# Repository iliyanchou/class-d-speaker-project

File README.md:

# Class-D Active Speaker Project

This repository presents my diploma engineering project: an active speaker system built around a Class-D amplifier.

## Overview

The project focuses on the design and practical implementation of an active speaker with efficient amplification, wireless audio input, analog input, tone control, and support for external subwoofer connection.

The system combines electronics, acoustics, amplifier theory, digital audio concepts, Bluetooth communication, power supply design, and physical construction.

## Main goals

* Build an active speaker with good sound quality and low distortion
* Use a Class-D amplifier for high efficiency and compact design
* Support Bluetooth audio and AUX input
* Add tone correction and signal control
* Design a portable and practical physical construction
* Document the theory, implementation, and testing process

## Key technologies and topics

* Class-D audio amplification
* PWM-based signal amplification
* Speaker and acoustic enclosure basics
* DSP and digital/analog audio conversion
* Bluetooth audio transmission
* Power supply and battery pack design
* Practical hardware assembly

## Documentation

The full diploma documentation is available in the `docs/` folder.

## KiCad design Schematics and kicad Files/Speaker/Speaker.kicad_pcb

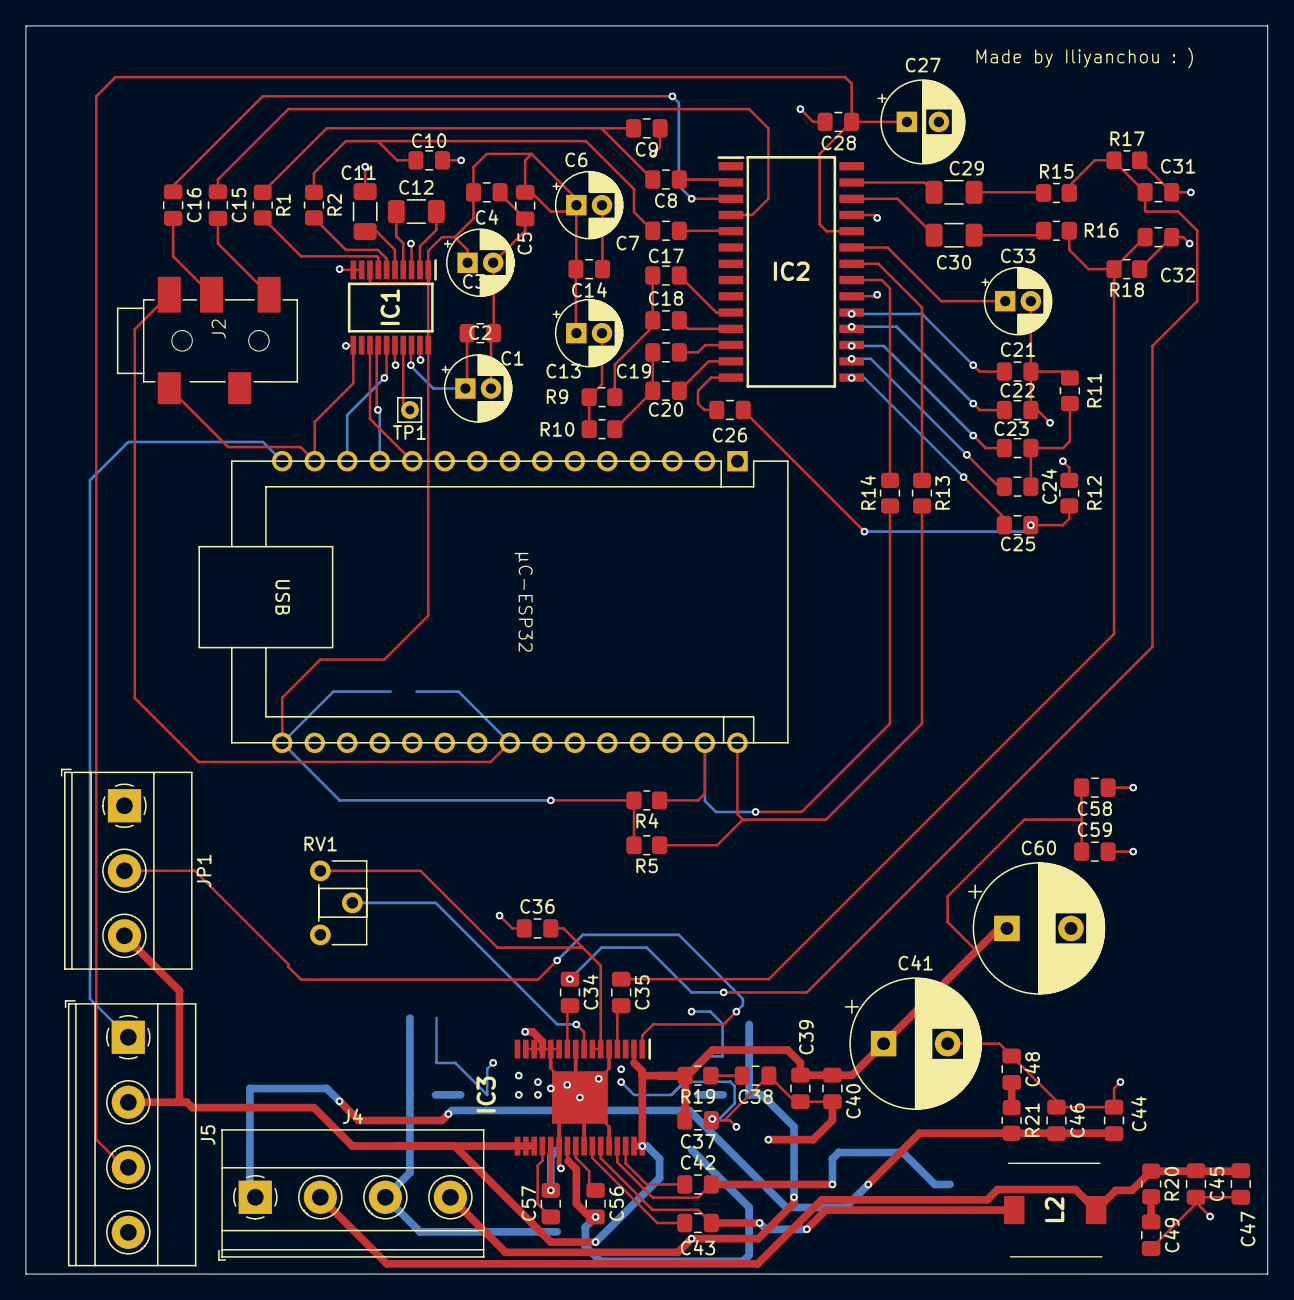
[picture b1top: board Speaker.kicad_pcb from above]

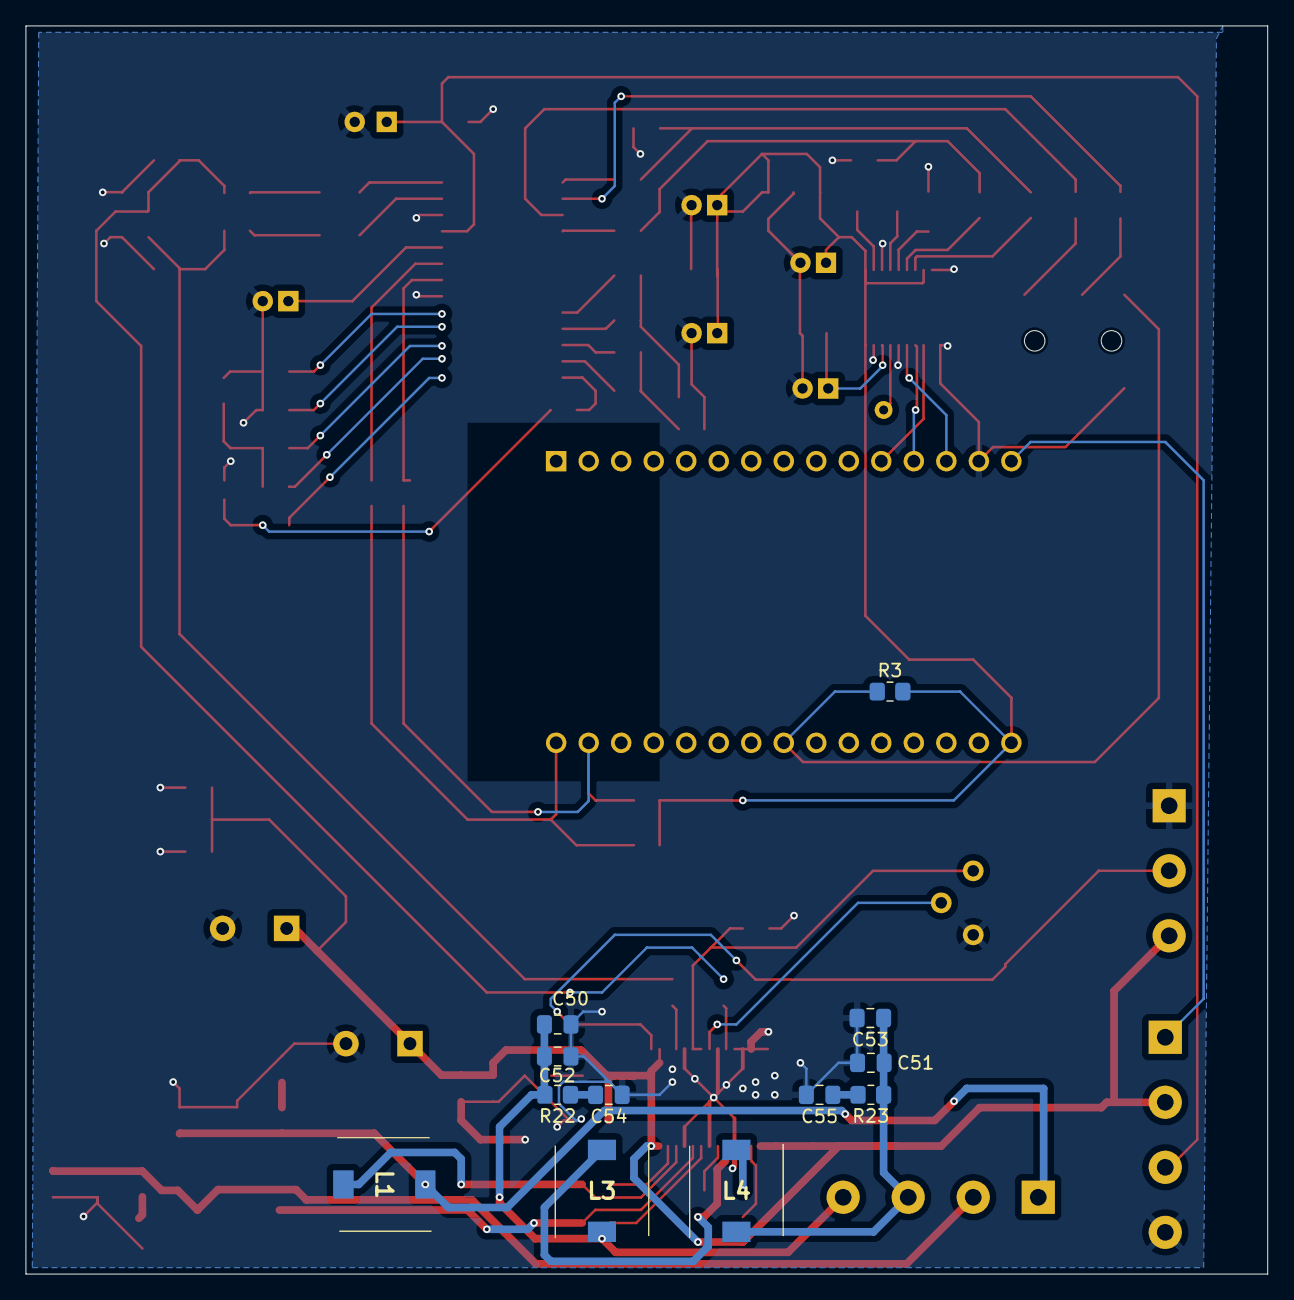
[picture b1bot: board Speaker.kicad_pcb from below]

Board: 2 copper layers, 97.0 x 97.5 mm, 94 parts (12 on the bottom side), 71 nets.

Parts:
C1, C3, C6, C13, C33: 10µF; CP_Radial_D5.0mm_P2.00mm
C2, C4, C5, C14, C19, C20, C25, C26, C28, C38, C40, C59: 100nF; C_0805_2012Metric_Pad1.18x1.45mm_HandSolder
C7, C8, C15, C16: 470nF; C_0805_2012Metric_Pad1.18x1.45mm_HandSolder
C9, C10: 2.2nF; C_0805_2012Metric_Pad1.18x1.45mm_HandSolder
C11, C12, C29, C30: 2.2µF; C_1206_3216Metric_Pad1.33x1.80mm_HandSolder
C17, C23: 18nF; C_0805_2012Metric_Pad1.18x1.45mm_HandSolder
C18, C24: 22nF; C_0805_2012Metric_Pad1.18x1.45mm_HandSolder
C21, C22: 5.6nF; C_0805_2012Metric_Pad1.18x1.45mm_HandSolder
C27: 47µF; CP_Radial_D6.3mm_P2.50mm
C31, C32, C39, C46, C47, C52, C53, C58: 1nF; C_0805_2012Metric_Pad1.18x1.45mm_HandSolder
C34, C35, C36: 1µF; C_0805_2012Metric_Pad1.18x1.45mm_HandSolder
C37, C48, C49, C54, C55: 10nF; C_0805_2012Metric_Pad1.18x1.45mm_HandSolder
C41, C60: 220µF; CP_Radial_D10.0mm_P5.00mm
C42, C43, C56, C57: 220nF; C_0805_2012Metric_Pad1.18x1.45mm_HandSolder
C44, C45, C50, C51: 680nF; C_0805_2012Metric_Pad1.18x1.45mm_HandSolder
IC1: PCM5102APWR; SOP65P640X120-20N
IC2: TDA7439DS13TR; SOIC127P1032X265-28N
IC3: TPA3129D2DAP; SOP65P810X120-33N
J2: Jack
J4, J5: Screw_Terminal_01x04; TerminalBlock_Phoenix_MKDS-1,5-4-5.08_1x04_P5.08mm_Horizont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
JP1: Jumper_3_Bridged12; TerminalBlock_Phoenix_MKDS-1,5-3-5.08_1x03_P5.08mm_Horizont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
L1, L2, L3, L4: 10µH; CDRH74NP220MCB
R1, R2, R13, R14: 470Ω; R_0805_2012Metric_Pad1.20x1.40mm_HandSolder
R3: 4.7kΩ; R_0805_2012Metric_Pad1.20x1.40mm_HandSolder
R4, R5, R17, R18: 10kΩ; R_0805_2012Metric_Pad1.20x1.40mm_HandSolder
R9, R11: 2.7kΩ; R_0805_2012Metric_Pad1.20x1.40mm_HandSolder
R10, R12: 5.6kΩ; R_0805_2012Metric_Pad1.20x1.40mm_HandSolder
R15, R16: 100Ω; R_0805_2012Metric_Pad1.20x1.40mm_HandSolder
R19: 33Ω; R_0805_2012Metric_Pad1.20x1.40mm_HandSolder
R20, R21, R22, R23: 3.3Ω; R_0805_2012Metric_Pad1.20x1.40mm_HandSolder
RV1: 120kΩ; Potentiometer_ACP_CA6-H2,5_Horizontal
TP1: MUTE; Pin_D0.7mm_L6.5mm_W1.8mm_FlatFork
µC-ESP32: ESP32

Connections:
3V3: C3.1, C4.2, C5.2, C6.1, C13.1, C14.2, IC1.1 (CPVDD), IC1.8 (AVDD), IC1.20 (DVDD), R3.2, R4.2, R5.2, µC-ESP32.1 (3v3)
5VCC: J5.1, µC-ESP32.30 (VIN)
9V VCC: C27.1, C28.1, IC2.24 (VS), J5.3
15VCC: C37.2, C39.2, C40.1, C41.1, C58.2, C59.1, C60.1, IC3.2 (SDZ), IC3.17 (AVCC), IC3.18 (PVCC_1), IC3.19 (PVCC_2), IC3.31 (PVCC_3), IC3.32 (PVCC_4), J5.2, JP1.3 (B), R19.2
GND: C1.2, C2.1, C3.2, C4.1, C5.1, C6.2, C9.1, C10.1, C11.1, C13.2, C14.1, C21.2, C22.2, C27.2, C28.2, C31.1, C32.2, C33.2, C36.1, C37.1, C38.1, C39.1, C40.2, C41.2, C44.1, C45.2, C46.1, C47.2, C48.1, C49.2, C50.1, C51.2, C52.1, C53.2, C54.1, C55.2, C58.1, C59.2, C60.2, IC1.3 (CPGND), IC1.9 (AGND), IC1.10 (DEMP), IC1.11 (FLT), IC1.16 (FMT), IC1.19 (DGND), IC2.20 (DIG-GND), IC2.25 (AGND), IC3.5 (RINN), IC3.9 (GND_1), IC3.11 (LINN), IC3.12 (MUTE), IC3.13 (AM2), IC3.14 (AM1), IC3.15 (AM0), IC3.22 (GND_2), IC3.25 (GND_3), IC3.28 (GND_4), IC3.33 (EP), J2.1 (GND), J5.4, JP1.1 (A), R9.2, R10.1, R11.2, R12.2, R17.2, R18.1, RV1.3, µC-ESP32.29 (GND)
unnamed: C8.2, C9.2, R1.1
unnamed: C7.2, C10.2, R2.1
unnamed: C17.1, C18.1, R9.1
unnamed: C19.1, C20.1, R10.2
unnamed: C23.2, C24.2, R11.1
unnamed: C25.2, C26.1, R12.1
unnamed: C29.2, R15.1
unnamed: C30.2, R16.1
unnamed: C31.2, C34.1, R15.2, R17.1
unnamed: C32.1, C35.1, R16.2, R18.2
unnamed: C38.2, R19.1
unnamed: C48.2, R21.1
unnamed: C49.1, R20.2
unnamed: C54.2, R22.1
unnamed: C55.1, R23.2
unnamed: IC1.13 (BCK), µC-ESP32.26 (D14)
unnamed: C12.1, IC1.4 (CAPM)
unnamed: C12.2, IC1.2 (CAPP)
unnamed: IC1.14 (DIN), µC-ESP32.27 (D12)
unnamed: C1.1, C2.2, IC1.18 (LDOO)
unnamed: IC1.15 (LRCK), µC-ESP32.28 (D13)
unnamed: IC1.6 (OUTL), R2.2
unnamed: IC1.7 (OUTR), R1.2
unnamed: C11.2, IC1.5 (VNEG)
unnamed: IC1.17 (XSMT), TP1.1
unnamed: C26.2, IC2.14 (BIN(L))
unnamed: C19.2, IC2.12 (BIN(R))
unnamed: C25.1, IC2.15 (BOUT(L))
unnamed: C20.2, IC2.13 (BOUT(R))
unnamed: C33.1, IC2.23 (CREF)
unnamed: C29.1, IC2.27 (LOUT)
unnamed: C15.1, IC2.4 (L_IN1)
unnamed: C7.1, IC2.5 (L_IN2)
unnamed: C23.1, IC2.17 (MIN(L))
unnamed: C17.2, IC2.10 (MIN(R))
unnamed: C24.1, IC2.16 (MOUT(L))
unnamed: C18.2, IC2.11 (MOUT(R))
unnamed: C30.1, IC2.26 (ROUT)
unnamed: C16.1, IC2.3 (R_IN1)
unnamed: C8.1, IC2.2 (R_IN2)
unnamed: IC2.21 (SCL), R14.2
unnamed: IC2.22 (SDA), R13.1
unnamed: C22.1, IC2.18 (TREBLE(L))
unnamed: C21.1, IC2.19 (TREBLE(R))
unnamed: C57.1, IC3.20 (BSNL)
unnamed: C43.1, IC3.26 (BSNR)
unnamed: C56.1, IC3.24 (BSPL)
unnamed: C42.1, IC3.30 (BSPR)
unnamed: IC3.8 (GAIN/SLV), RV1.2
unnamed: C36.2, IC3.6 (PLIMIT), IC3.7 (GVDD), RV1.1
unnamed: C34.2, IC3.10 (LINP)
unnamed: IC3.1 (MODSEL), JP1.2 (C)
unnamed: C57.2, IC3.21 (OUTNL), L4.2
unnamed: C43.2, IC3.27 (OUTNR), L2.2
unnamed: C56.2, IC3.23 (OUTPL), L3.1
unnamed: C42.2, IC3.29 (OUTPR), L1.1
unnamed: C35.2, IC3.4 (RINP)
unnamed: J2.5 (DETECT), R3.1, µC-ESP32.8 (D5)
unnamed: C15.2, J2.4 (L)
unnamed: C16.2, J2.3 (R)
unnamed: C44.2, C46.2, J4.1, L1.2, R21.2
unnamed: C45.1, C47.1, J4.2, L2.1, R20.1
unnamed: C51.1, C53.1, J4.3, L4.1, R23.1
unnamed: C50.2, C52.2, J4.4, L3.2, R22.2
unnamed: R4.1, R14.1, µC-ESP32.14 (D22)
unnamed: R5.1, R13.2, µC-ESP32.15 (D23)

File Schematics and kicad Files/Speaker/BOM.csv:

"Reference","Value","Datasheet","Footprint","Qty","DNP"
"4S1","14.8V / 3700mAh","~","","1",""
"AMSRL1-7805JZ1,J2,µC-ESP32","~","","-- mixed values --","3",""
"C1,C3,C6,C13,C33,C62,C63,C64","10µF","~","-- mixed values --","8",""
"C2,C4,C5,C14,C19,C20,C25,C26,C28,C38,C40,C59,C66,C67","100nF","~","Capacitor_SMD:C_0805_2012Metric_Pad1.18x1.45mm_HandSolder","14",""
"C7,C8,C15,C16","470nF","~","Capacitor_SMD:C_0805_2012Metric_Pad1.18x1.45mm_HandSolder","4",""
"C9,C10","2.2nF","~","Capacitor_SMD:C_0805_2012Metric_Pad1.18x1.45mm_HandSolder","2",""
"C11,C12,C29,C30","2.2µF","~","Capacitor_SMD:C_1206_3216Metric_Pad1.33x1.80mm_HandSolder","4",""
"C17,C23","18nF","~","Capacitor_SMD:C_0805_2012Metric_Pad1.18x1.45mm_HandSolder","2",""
"C18,C24","22nF","~","Capacitor_SMD:C_0805_2012Metric_Pad1.18x1.45mm_HandSolder","2",""
"C21,C22","5.6nF","~","Capacitor_SMD:C_0805_2012Metric_Pad1.18x1.45mm_HandSolder","2",""
"C27","47µF","~","Capacitor_THT:CP_Radial_D6.3mm_P2.50mm","1",""
"C31,C32,C39,C46,C47,C52,C53,C58","1nF","~","Capacitor_SMD:C_0805_2012Metric_Pad1.18x1.45mm_HandSolder","8",""
"C34,C35,C36","1µF","~","Capacitor_SMD:C_0805_2012Metric_Pad1.18x1.45mm_HandSolder","3",""
"C37,C48,C49,C54,C55","10nF","~","Capacitor_SMD:C_0805_2012Metric_Pad1.18x1.45mm_HandSolder","5",""
"C41,C60","220µF","~","Capacitor_THT:CP_Radial_D10.0mm_P5.00mm","2",""
"C42,C43,C56,C57","220nF","~","Capacitor_SMD:C_0805_2012Metric_Pad1.18x1.45mm_HandSolder","4",""
"C44,C45,C50,C51","680nF","~","Capacitor_SMD:C_0805_2012Metric_Pad1.18x1.45mm_HandSolder","4",""
"C61","22µF","~","Capacitor_SMD:C_0805_2012Metric_Pad1.18x1.45mm_HandSolder","1",""
"C65","4.7µF","~","Capacitor_SMD:C_0805_2012Metric_Pad1.18x1.45mm_HandSolder","1",""
"IC1","PCM5102APWR","https://componentsearchengine.com/Datasheets/2/PCM5102APWR.pdf","Dip:SOP65P640X120-20N","1",""
"IC2","TDA7439DS13TR","https://www.st.com/resource/en/datasheet/tda7439ds.pdf","Dip:SOIC127P1032X265-28N","1",""
"IC3","TPA3129D2DAP","http://www.ti.com/lit/gpn/tpa3129d2","Dip:SOP65P810X120-33N","1",""
"J4","Screw_Terminal_01x04","~","TerminalBlock_Phoenix:TerminalBlock_Phoenix_MKDS-1,5-4-5.08_1x04_P5.08mm_Horizontal","1",""
"L1,L2,L3,L4,L5","10µH","~","-- mixed values --","5",""
"L6","12µH","~","","1",""
"LS1,RS1","8Ω","~","","2",""
"PS1","R-78E9.0-0.5","https://www.recom-power.com/pdf/Innoline/R-78Exx-0.5.pdf","R78E1205","1",""
"R1,R2,R13,R14","470Ω","~","Resistor_SMD:R_0805_2012Metric_Pad1.20x1.40mm_HandSolder","4",""
"R3","4.7kΩ","~","Resistor_SMD:R_0805_2012Metric_Pad1.20x1.40mm_HandSolder","1",""
"R4,R5,R17,R18","10kΩ","~","Resistor_SMD:R_0805_2012Metric_Pad1.20x1.40mm_HandSolder","4",""
"R6","1MΩ","~","Resistor_SMD:R_0805_2012Metric_Pad1.20x1.40mm_HandSolder","1",""
"R7,R8","5.1kΩ 1%","~","Resistor_SMD:R_0805_2012Metric_Pad1.20x1.40mm_HandSolder","2",""
"R9,R11","2.7kΩ","~","Resistor_SMD:R_0805_2012Metric_Pad1.20x1.40mm_HandSolder","2",""
"R10,R12","5.6kΩ","~","Resistor_SMD:R_0805_2012Metric_Pad1.20x1.40mm_HandSolder","2",""
"R15,R16","100Ω","~","Resistor_SMD:R_0805_2012Metric_Pad1.20x1.40mm_HandSolder","2",""
"R19","33Ω","~","Resistor_SMD:R_0805_2012Metric_Pad1.20x1.40mm_HandSolder","1",""
"R20,R21,R22,R23","3.3Ω","~","Resistor_SMD:R_0805_2012Metric_Pad1.20x1.40mm_HandSolder","4",""
"RV1","120kΩ","~","Potentiometer_THT:Potentiometer_ACP_CA6-H2,5_Horizontal","1",""
"RV2","100kΩ","~","","1",""
"TP1","MUTE","~","Connector_Pin:Pin_D0.7mm_L6.5mm_W1.8mm_FlatFork","1",""

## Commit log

2026-06-24 inital commit
2026-06-25 added all files
